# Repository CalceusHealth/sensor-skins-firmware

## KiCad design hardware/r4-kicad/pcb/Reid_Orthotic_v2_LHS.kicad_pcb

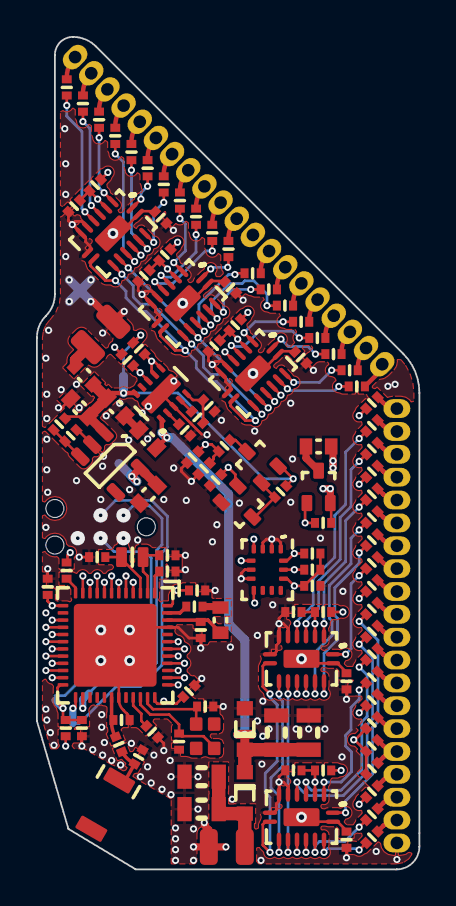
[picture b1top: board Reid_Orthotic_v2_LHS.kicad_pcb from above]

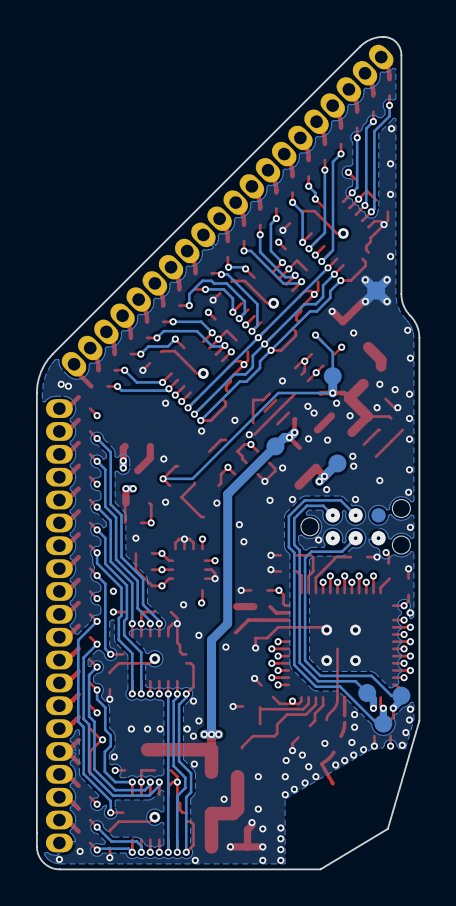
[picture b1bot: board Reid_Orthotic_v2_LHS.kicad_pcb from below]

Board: 4 copper layers, 21.2 x 46.2 mm, 130 parts (8 on the bottom side), 122 nets.

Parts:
ANT1: AMCA31-2R450G-S1F-T3; RFANT3216120A5T
C1, C2, C3, C6, C8, C10, C24, C25, C26, C27, C28: 100n; 0402_CAP_HD
C4, C5, C11, C12: 12p; 0402_CAP_HD
C7, C9: 1u; 0402_CAP_HD
C13: 100p; 0402_CAP_HD
C15: 1.5p; 0402_CAP_HD
C16, C18, C22, C23: DNF; 0402_CAP_HD
C19, C20, C21: 10n; 0402_CAP_HD
C34, C35, C39, C43: 4.7u; 0603_CAP_HD
C37: 33n C0G; 0805_CAP
C38: DNF; 0805_CAP
C40, C42: 100u; 0805_CAP
D1: CUS08F30,H3F; SOD-323
D2: MM3Z5V1T1G; SOD-323
F1: 200mA; 0603_FUSE
J1, J2: IO_CONN
J3: RF_CONN
J4: BAT_CONN
L1: 15nH HK100515NJ-T; 0402_HD
L2: 10uH LBMF1608T100K; 0603_HD
L3: 3.9nH LQP15MN3N9B02D; 0402_HD
NP1, NP2, NP3: NPTH; NPTH_1mm
PAD1: VSYS; PAD_VSYS_1
PAD2: SWDIO; PAD_SWDIO_2
PAD3: 3V3; PAD_3V3_3
PAD4: MCU_RST; PAD_MCU_RST_4
PAD5: 0V; PAD_0V_5
PAD6: VBAT_F; PAD_VBAT_F_6
PAD7: SWDCLK; PAD_SWDCLK_7
PAD8: NET146; PAD_NET146_8
Q1: BSS816NW; SOT323
Q2: DMP2110UW; SOT323
Q3: RU1C002ZP; SOT323
R1, R2, R3, R4, R5, R6, R7, R8, R9, R10, R11, R12, R13, R14, R15, R16, R17, R18, R19, R21, R22, R23, R24, R25, R26, R27, R28, R29, R30, R31, R32, R33, R34, R35, R36, R37, R38: 100R; 0402_RES_HD
R20, R41, R42, R43, R44, R45, R57, R61, R62: 100k; 0402_RES_HD
R39, R40: 2.1k; 0402_RES_HD
R46: 1M; 0402_RES_HD
R47, R48, R49: 10k; 0402_RES_HD
R50, R51, R58: DNF; 0402_RES_HD
R54: 10R; 0603_RES_HD
R55, R56: 5.1k; 0402_RES_HD
R59: 22k; 0402_RES_HD
R60: NCU15XH103F60RC; 0402_RES_HD
U1: LSM6DSM
U2: NRF52832-QFAA
U3, U4, U5, U6, U7: 74LV4051BQ
U8: BQ24210
U9: ?TCR3UF33A,LM(CT; SOT23-5
X1: 32.768kHz NX1610SA; CRYSTAL_NDK_NX1610SA
X2: 32MHz XRCGB32M; XTAL_2016

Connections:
0V: C1.1, C2.2, C3.1, C4.2, C5.2, C6.1, C7.1, C8.1, C9.1, C10.1, C11.1, C12.1, C13.1, C15.1, C16.1, C18.2, C19.2, C20.2, C21.2, C22.2, C23.2, C24.1, C25.1, C26.1, C27.1, C28.1, C34.1, C35.1, C37.1, C38.1, C39.1, C40.1, C42.1, C43.1, D2.1, J1.15, J2.1, J2.5, J3.1, J4.1, PAD5.1, Q1.2, R41.2, R44.2, R55.2, R56.2, R58.2, R60.1, U1.1, U1.2, U1.3, U1.6, U1.7, U2.31, U2.45, U2.PAD, U3.6, U3.7, U3.8, U4.6, U4.7, U4.8, U5.6, U5.7, U5.8, U6.6, U6.7, U6.8, U7.6, U7.7, U7.8, U8.3, U8.PAD, U9.2
3V3: C1.2, C7.2, C8.2, C10.2, C39.2, PAD3.1, Q3.2, R39.2, R40.2, R45.2, R46.2, R61.1, U1.5, U1.8, U1.12, U2.13, U2.36, U2.48, U9.5
ADC_VBAT: C2.1, R43.2, R44.1, U2.7
ANT_FEED: C15.2, L3.1, U2.30
BQ_CHG: R61.2, U2.15, U8.8
BQ_PG: R20.1, U2.12
CAP_CH0: C22.1, R50.1, U2.42, U6.3
CAP_CH1: C23.1, R51.1, U2.40, U7.3
CAP_S0: U2.16, U6.11, U7.11
CAP_S1: U2.17, U6.10, U7.10
CAP_S2: U2.18, U6.9, U7.9
DCC: L1.2, U2.47
DEC1: C6.2, U2.1
DEC3: C13.2, U2.33
DEC4: C9.2, L2.2, U2.46
FSR_CH0: C19.1, R47.1, U2.6, U3.3
FSR_CH1: C20.1, R48.1, U2.5, U4.3
FSR_CH2: C21.1, R49.1, U2.4, U5.3
FSR_S0: U2.11, U3.11, U4.11, U5.11
FSR_S1: U2.10, U3.10, U4.10, U5.10
FSR_S2: U2.9, U3.9, U4.9, U5.9
MCU_RST: C3.2, PAD4.1, R45.1, U2.24
MUX_ON: Q3.1, R46.1, U2.43
MUX_VCC: C24.2, C25.2, C26.2, C27.2, C28.2, R47.2, R48.2, R49.2, R50.2, R51.2, R54.1, U3.16, U3.PAD, U4.16, U4.PAD, U5.16, U5.PAD, U6.16, U6.PAD, U7.16, U7.PAD
NET7: R20.2, R62.2, U8.6, U8.7
NET17: C37.2, C38.2, D1.1, J3.2
NET18: ANT1.2, C16.2, L3.2
NET29: Q1.3, Q2.1, R42.2
NET34: R59.2, R60.2, U8.5
NET36: R57.1, R58.1, U9.3
NET37: J1.11, R19.2
NET38: J1.1, R18.2
NET39: J1.5, R10.2
NET40: J1.16, R9.2
NET41: J1.17, R8.2
NET42: J1.8, R7.2
NET43: J1.9, R6.2
NET44: J1.18, R5.2
NET45: J1.19, R4.2
NET46: U1.4, U2.37
NET47: J1.10, R3.2
NET50: J1.6, R2.2
NET53: J1.20, R1.2
NET55: J1.2, R17.2
NET56: J2.2, R38.2
NET57: J2.3, R37.2
NET58: J2.4, R36.2
NET59: J2.6, R35.2
NET60: J2.7, R34.2
NET61: J2.8, R33.2
NET62: J2.9, R32.2
NET63: J2.10, R31.2
NET64: J1.12, R16.2
NET65: J2.11, R30.2
NET66: J2.12, R29.2
NET67: J2.13, R28.2
NET68: J2.14, R27.2
NET69: J2.15, R26.2
NET70: J2.16, R25.2
NET71: J2.17, R24.2
NET72: J2.18, R23.2
NET73: J2.19, R22.2
NET74: J2.20, R21.2
NET75: J1.13, R15.2
NET76: J1.7, R14.2
NET77: J1.3, R13.2
NET78: J1.14, R12.2
NET79: J1.4, R11.2
NET80: R23.1, U6.4
NET81: R22.1, U6.5
NET82: R25.1, U6.2
NET83: R27.1, U6.15
NET84: R26.1, U6.14
NET85: R28.1, U6.1
NET86: R31.1, U7.5
NET87: R32.1, U7.4
NET88: R38.1, U7.15
NET89: R30.1, U7.1
NET90: R33.1, U7.2
NET91: R37.1, U7.14
NET92: R19.1, U5.14
NET93: R18.1, U5.15
NET94: R17.1, U5.1
NET95: R16.1, U5.4
NET96: R15.1, U5.2
NET97: R13.1, U4.15
NET98: R14.1, U4.14
NET99: R12.1, U4.12
NET100: R11.1, U4.1
NET101: R10.1, U4.5
NET102: R9.1, U4.4
NET103: R8.1, U4.2
NET104: R1.1, U3.5
NET105: R2.1, U3.4
NET106: R7.1, U3.15
NET107: R6.1, U3.1
NET108: R5.1, U3.14
NET109: R4.1, U3.12
NET110: R3.1, U3.2
NET112: R56.1, U8.2
NET113: Q2.3, R43.1
NET116: R59.1, U8.4
NET118: Q3.3, R54.2
NET119: L1.1, L2.1
SCL: R40.1, U1.13, U2.39
SDA: R39.1, U1.14, U2.38
SWDCLK: PAD7.1, U2.25
SWDIO: PAD2.1, U2.26
TEMP_COM: C18.1, R35.1, R55.1, U2.41
TEMP_S0: R24.1, U2.21
TEMP_S1: R21.1, U2.22
TEMP_S2: R29.1, U2.20
TEMP_S3: R34.1, U2.19
TEMP_S4: R36.1, U2.23
VBAT: F1.1, J4.2
VBAT_F: C35.2, C43.2, F1.2, PAD6.1, Q2.2, R42.1, R57.2, R62.1, U8.10, U9.1
VBAT_ON: Q1.1, R41.1, U2.8
VSYS: C34.2, C40.2, C42.2, D1.2, D2.2, PAD1.1, U8.1
XC1: C12.2, U2.34, X2.1
XC2: C11.2, U2.35, X2.3
XL1: C4.1, U2.2, X1.1
XL2: C5.1, U2.3, X1.2

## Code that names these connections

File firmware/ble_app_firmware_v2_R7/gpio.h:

/*===========================================
//
// gpio.h
// Written by Alex Gilmour
// Copyright (c) 2024, CarbonCircuits
// All rights reserved.
//
//=========================================*/

#ifndef GPIO_H_
#define GPIO_H_

#include <stdint.h>
#include "nrf_gpio.h"
#include "configure_firmware.h"
#include "system.h"
#include "nordic_common.h"
#include "nrf.h"

// adc pins
#define ADC_VDD			(NRF_SAADC_INPUT_VDD)

#ifdef REID_LHS
//#define PIN_MUX_ON		(25)
#define PIN_MUX_ON		(31)

#define PIN_FSR_CH0		(4)
#define PIN_FSR_CH1		(3)
#define PIN_FSR_CH2		(2)
#define ADC_FSR_CH0		(NRF_SAADC_INPUT_AIN2)
#define ADC_FSR_CH1		(NRF_SAADC_INPUT_AIN1)
#define ADC_FSR_CH2		(NRF_SAADC_INPUT_AIN0)
#define PIN_FSR_S0		(9)
#define PIN_FSR_S1		(8)
#define PIN_FSR_S2		(7)

#define PIN_CAP_CH0		(30)
#define PIN_CAP_CH1		(28)
#define ADC_CAP_CH0		(NRF_SAADC_INPUT_AIN6)
#define ADC_CAP_CH1		(NRF_SAADC_INPUT_AIN4)
#define PIN_CAP_S0		(13)
#define PIN_CAP_S1		(14)
#define PIN_CAP_S2		(15)

#define PIN_TEMP_S0		(18)
#define PIN_TEMP_S1		(19)
#define PIN_TEMP_S2		(17)
#define PIN_TEMP_S3		(16)
#define PIN_TEMP_S4		(20)
#define PIN_TEMP_COM	(29)
#define ADC_TEMP_COM	(NRF_SAADC_INPUT_AIN5)
//#define PIN_TEMPREF		(31)
//#define ADC_TEMPREF		(NRF_SAADC_INPUT_AIN7)

#define PIN_VBAT		(5)
#define ADC_VBAT		(NRF_SAADC_INPUT_AIN3)
#define PIN_VBAT_ON		(6)

#define PIN_BQ_PG		(10)
#define PIN_BQ_CHG		(12)

#define PIN_SDA			(26)
#define PIN_SCL			(27)
//#define PIN_6DOF_INT1	(25)

#define PIN_IS_LHS		(22)

#else
#ifdef REID_RHS
#define PIN_MUX_ON		(31)

#define PIN_FSR_CH0		(2)
#define PIN_FSR_CH1		(3)
#define PIN_FSR_CH2		(4)
#define ADC_FSR_CH0		(NRF_SAADC_INPUT_AIN0)
#define ADC_FSR_CH1		(NRF_SAADC_INPUT_AIN1)
#define ADC_FSR_CH2		(NRF_SAADC_INPUT_AIN2)
#define PIN_FSR_S0		(27)
#define PIN_FSR_S1		(26)
#define PIN_FSR_S2		(25)

#define PIN_CAP_CH0		(30)
#define PIN_CAP_CH1		(28)
#define ADC_CAP_CH0		(NRF_SAADC_INPUT_AIN6)
#define ADC_CAP_CH1		(NRF_SAADC_INPUT_AIN4)
#define PIN_CAP_S0		(15)
#define PIN_CAP_S1		(14)
#define PIN_CAP_S2		(13)

#define PIN_TEMP_S0		(17)
#define PIN_TEMP_S1		(16)
#define PIN_TEMP_S2		(18)
#define PIN_TEMP_S3		(20)
#define PIN_TEMP_S4		(19)
#define PIN_TEMP_COM	(29)
#define ADC_TEMP_COM	(NRF_SAADC_INPUT_AIN5)
//#define PIN_TEMPREF		()
//#define ADC_TEMPREF		(NRF_SAADC_INPUT_AIN)

#define PIN_VBAT		(5)
#define ADC_VBAT		(NRF_SAADC_INPUT_AIN3)
#define PIN_VBAT_ON		(6)

#define PIN_BQ_PG		(10)
#define PIN_BQ_CHG		(11)

#define PIN_SDA			(8)
#define PIN_SCL			(9)
//#define PIN_6DOF_INT1	(11)

#define PIN_IS_LHS		(22)

#else
#error No side defined for pinout
#endif
#endif

#define PIN_RESET		(21)

void gpio_init(void);
void gpio_deinit(void);

uint8_t gpio_bq_chg_asserted(void);
uint8_t gpio_bq_pg_asserted(void);


#endif // GPIO_H_ 

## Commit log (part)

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2026-04-29 Import Alex firmware source baselines
2026-04-29 Add Tim firmware branch sources, tooling, and docs
2026-04-29 Move duplicate Alex imports into staging folder
2026-04-29 Add release steps and sleep logic docs
2026-05-01 Track firmware variants and add binary stream scaffold
2026-05-01 Pin v00020023 build matrix to release commit
2026-05-01 Ignore local alex extracts and codex state
2026-05-02 Increase recharge coil PWM duty cycle from 25 to 75 (10.5% → 31.6%) in R3
    coil_set_power(25) was only driving the coil at ~10.5% duty cycle, well below
    the hardware ceiling. Raising to 75 gives ~3x more power transfer and should
    significantly reduce battery recharge time. Max supported by the current PWM
    config is coil_set_power(100) (~43.9% duty cycle).
    Note: validate thermal performance on hardware before going higher than 75.
    https://claude.ai/code/session_018A5rwa6DpqvDck9dbqB9Wy
2026-05-02 Fix device stuck in sleep mode after low-battery recharge
    When battery drains to ~3V while the device is not being worn, the FSR-based
    sleep mode activates and stops BLE advertising. Because the brownout detector
    is disabled (system.c), the nRF52 never resets — it just keeps polling FSR
    sensors every 5 seconds indefinitely. When the device is then recharged, it
    remains in the sleep loop since no foot pressure is detected, leaving it
    permanently invisible to nRF Connect.
2026-05-02 Add watchdog timer to recover from frozen RTC/sleep states
    Without a WDT, if the RTC peripheral stops (e.g. due to a low-voltage event
    with brownout detection disabled), system_time_ms() freezes and the timing
    loop in system_sleep() parks the CPU in WFE indefinitely with no recovery path.
    Standing on the FSR sensors has no effect because measure_sensors() is never
    reached.
    WDT is configured to run during CPU sleep (SLEEP_Run) with a 60-second timeout.
2026-05-04 Add watchdog timer to recover from frozen sleep states
    Without a WDT, if the firmware stalls in WFE (e.g. RTC peripheral stops
    responding, or any non-hardfault hang) the chip stays alive but never
    reaches measure_sensors() or restarts advertising. Charging does not
    recover from this state -- only a full battery drain triggers POR.
    WDT runs during CPU sleep with a 60-second timeout. system_wdt_kick()
    is called at the top of system_sleep() so any stalled WFE loop that goes
2026-05-04 Increase recharge coil PWM duty cycle from 25 to 75 in R3 charger
    coil_set_power(25) drove the coil at ~10.5% duty cycle, well below the
    hardware ceiling. coil_set_power(75) gives ~31.6% duty (~3x more power
    transfer) and significantly reduces battery recharge time. A weak puck
    output is the leading hypothesis for several devices entering the
    'dark, charged, but not advertising' state -- a brief VSYS collapse
    during charging with the previous puck duty cycle could damage the 3V3
2026-05-04 Add BLE 'lifeline' slow advertising during sleep states
    Previously enter_device_sleep() called ble_reid_force_disconnect() which
    stopped advertising entirely. Combined with the FSR-only wake conditions
    in the sleep loop, a device that enters sleep while not being worn
    (e.g. on the charger after the 15-second charging-confirmed idle window)
    becomes invisible to nRF Connect and the mobile app -- recoverable only
    by standing on the orthotic. This blocks bench diagnosis and field
2026-05-04 Bump DEVICE_FW_VERSION to v00020024
    Includes watchdog (9f7999f), coil PWM 25->75 (fe16f70), and BLE
    lifeline (3d6b019). Distinct from v00020023 which had none of these
    firmware-resilience changes.
2026-05-29 Added compiled firmware to Git
2026-06-03 Revert "Wire up LSM6DSM IMU bring-up (v00020025)"
    This reverts commit f6d7ca9ae6d7778bc31c2190380523605f842107.
2026-06-04 Add GitHub Actions workflow to build + publish Sensor Skins DFU packages
    Builds the R7 application for all live variants ({lhs,rhs} x {stream,nostream},
    sleep on) on an Ubuntu runner using the existing tools/*.sh scripts: downloads
    and caches the nRF5 SDK 15.3.0 and SEGGER Embedded Studio (free Nordic edition,
    emBuild needs no license), installs nrfutil, signs the DFU zips, and publishes
    them.
    Outputs are uploaded as workflow artifacts on every run, and on tim pushes a
2026-06-04 Add cloud-build setup checklist; correct BUILDING.md key note
    Clarify in BUILDING.md that calceus_private.key is .gitignored and must be
    present locally (or supplied via the CALCEUS_DFU_PRIVATE_KEY CI secret), rather
    than committed to the repo.
    Add SETUP_CLOUD_BUILDS.md: a step-by-step checklist for enabling the GitHub
    Actions firmware builds from a local machine (locate the signing key, add the
    secret, merge the workflow to tim, verify, and field usage).
